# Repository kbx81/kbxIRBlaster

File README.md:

# kbx IR Blaster

## What?

Just another ESP32-based IR Blaster. It was designed with [ESPHome](https://esphome.io) in mind but should work fine
with [Tasmota](https://tasmota.github.io/docs/) or any other app, really.

I've created four versions:
- [v4](v4/)
  - Based on ESP32-C6
  - Nearly identical to [v3](v3/) (below) but with minor adjustments/enhancements
- [v3](v3/)
  - Based on ESP32-C3
  - Disc (smaller)
  - One header for (an) off-board emitter(s)
  - Pads for 24 IR LEDs:
    - Eight top-emitting surface mount
    - Eight side-emitting surface mount around the edges of the disc
    - Eight 5 mm LEDs for extra "throw"
- [v2](v2/)
  - Based on ESP32
  - Disc
  - One header for (an) off-board emitter(s)
  - Pads for 16 IR LEDs:
    - Eight top-emitting surface mount
    - Eight 5 mm LEDs for extra "throw" around the perimeter of the PCB
- [v1](v1/)
  - Based on ESP32
  - Rectangular
  - One header for up to four external control channels
  - Pads for up to eight through-hole LEDs, front- and/or back-facing

See the [gallery](GALLERY.md) for more images.

## Why?

After trying this on a perfboard with parts I had laying around, I wanted something more polished and more powerful.
I found [Sparkfun's IR Blaster](https://www.sparkfun.com/products/15031) which is quite nice, tiny and clean but I
quickly realized that its IR output is somewhat weak and would only work if pointed _directly_ at the device it was
intended to control. Rather than hack it up, I chose to draw up my own versions of such a thing. My goal was to make
them substantially more powerful in an effort to "light up a room" with infrared light; that is, you'll probably find
that they work well even when not specifically directed at (if even near) devices you wish to control. I've used an
ESP32 module instead of an ESP8266, as the ESP32 (and its variants) has dedicated hardware for IR data transmission
(the RMT) which makes it more suitable for this purpose, despite that it's otherwise quite overkill.

## How?

Please see the bill of materials (BoM) for the version of interest:
 -  v4 BoM: [Octopart](https://octopart.com/bom-tool/P6YqtNWD), [CSV](v4/kbxIrBlaster_bom.csv)
 -  v3 BoM: [Octopart](https://octopart.com/bom-tool/GUsHZQub), [CSV](v3/kbxIrBlaster_bom.csv)
 -  v2 BoM: [Octopart](https://octopart.com/bom-tool/78rYOXWE), [CSV](v2/kbxIrBlaster_bom.csv)
 -  v1 BoM: [Octopart](https://octopart.com/bom-tool/vDwq4wDr), [CSV](v1/kbxIrBlaster_bom.csv)

I had the PCBs fabricated by [Elecrow](https://www.elecrow.com) but nearly any PCB fabricator should be able to
manufacture these without any issues. I do recommend white soldermask as it will reflect IR best.

The schematic and PCB were drawn in [KiCad](https://www.kicad.org).

## Build Notes

The [v1](v1/) and [v2](v2/) PCBs have a number of solder jumpers on the bottom side that enable each of the FET drivers
to be connected to one of two possible GPIO pins. This allows a single GPIO pin to control all LEDs simultaneously or
they can be broken apart onto separate GPIO pins. Labels on the underside of the PCBs indicate what jumpers are
connected to what LEDs.

_Note that the solder jumpers **must be bridged** one way or the other; if this is not done, the FETs (and consequently
the LEDs they drive) will not activate!_ When you build one, be sure to complete this step or you'll be left in the
dark. (Punny, I know.)

## Add-ons

An FS1000A (such as [this one](https://www.amazon.com/HiLetgo-Wireless-Transmitter-Receiver-Raspberry/dp/B01DKC2EY4/))
or similar 433 MHz transmitter module may be connected as indicated on the PCB allowing the device to double as an RF
remote controller. On the [v1](v1/) PCB, bridge JP6 to enable this and then connect the module to pins 4, 5, and 6 on
J2. On the [v2](v2/) PCB, simply connect the transmitter to J8. When doing so, be sure to orient the module correctly
or tragedy may result.

## Usage

See my [ESPHome-configs](https://github.com/kbx81/esphome-configs) repository for example
[ESPHome](https://esphome.io) configuration you may use with your IR blaster. Enjoy!

 ## Legal stuff and License

The circuit schematics and PCB found here are licensed under the
 [Creative Commons Attribution-ShareAlike 4.0 International License](http://creativecommons.org/licenses/by-sa/4.0/).

_Happy building!_

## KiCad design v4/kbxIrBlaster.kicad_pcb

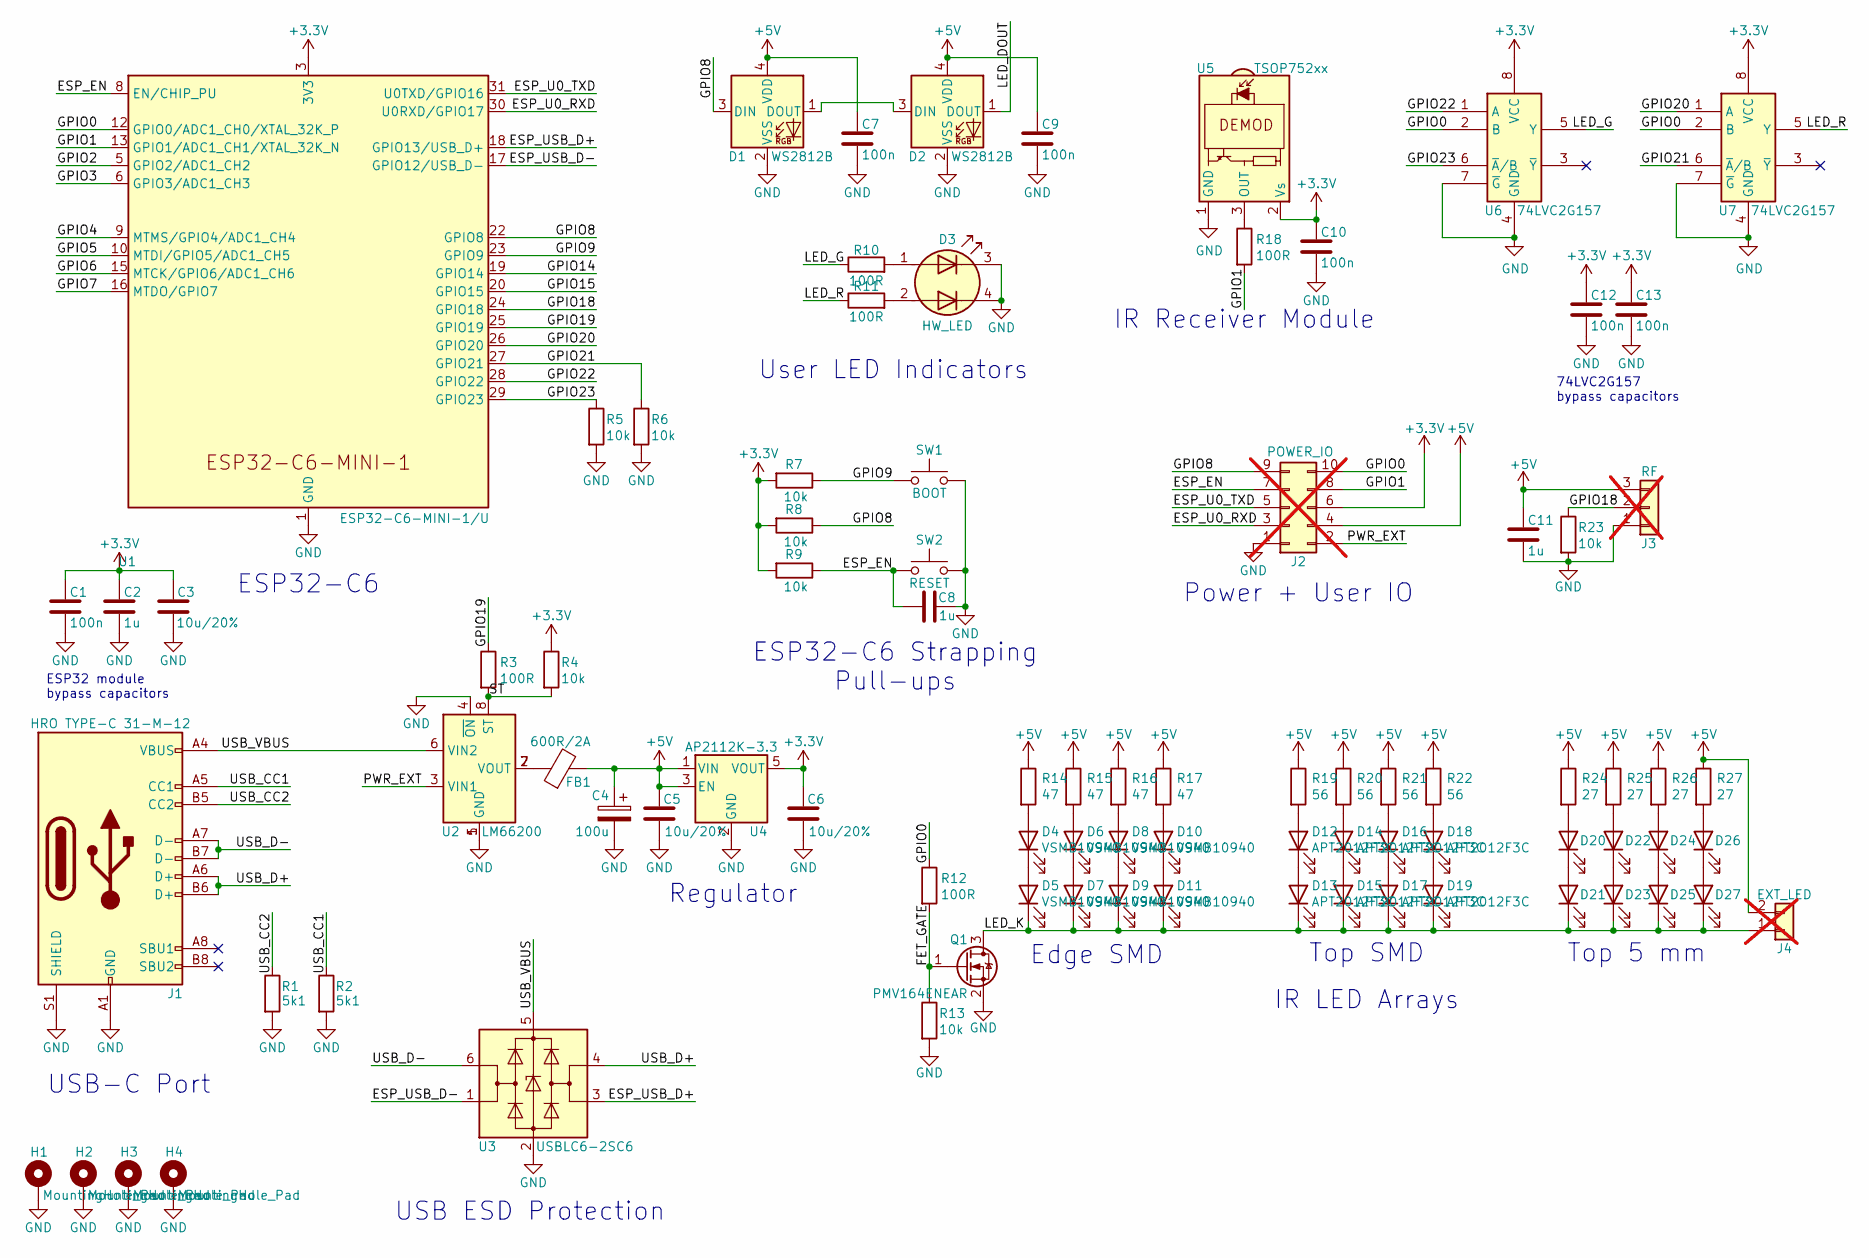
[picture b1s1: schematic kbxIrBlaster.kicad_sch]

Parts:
C1, C7, C9, C10, C12, C13: 100n; C_0402_1005Metric; MPN1 CC0402KRX5R6BB104
C2, C8, C11: 1u; C_0402_1005Metric; MPN1 CC0402KRX5R6BB105
C3, C5, C6: 10u/20%; C_0603_1608Metric; MPN1 CC0603MRX5R6BB106
C4: 100u; CP_Elec_5x5.4; MPN1 UWR1A101MCL1GB
D1, D2: WS2812B; LED_WS2812B-2020_PLCC4_2.0x2.0mm; MPN1 WS2812B-2020
D3: HW_LED; LED_Cree-PLCC4_3.2x2.8mm_CCW; MPN1 APB3227SURKZGC
D4, D5, D6, D7, D8, D9, D10, D11: VSMB10940; LED_Kingbright_KPA-3010_3x2x1mm; MPN1 VSMB10940
D12, D13, D14, D15, D16, D17, D18, D19: APT2012F3C; LED_0805_2012Metric; MPN1 APT2012F3C
D20, D21, D22, D23, D24, D25, D26, D27: LTE-4206; LED_D5.0mm; MPN1 LTE-4206
FB1: 600R/2A; L_0603_1608Metric; MPN1 MPZ1608S221ATA00
H1, H2, H3, H4: MountingHole_Pad; MountingHole_2.5mm_Pad_Via
J1: HRO TYPE-C 31-M-12; USB_C_Receptacle_HRO_TYPE-C-31-M-12; MPN1 HRO TYPE-C 31-M-12
J2: POWER_IO; PinSocket_2x05_P2.54mm_Vertical; not fitted
J3: RF; PinSocket_1x03_P2.54mm_Vertical; not fitted
J4: EXT_LED; PinSocket_1x02_P2.54mm_Vertical; not fitted
Q1: PMV164ENEAR; SOT-23; MPN1 PMV164ENEAR
R1, R2: 5k1; R_0402_1005Metric; MPN1 RC0402JR-075K1L
R3, R10, R11, R12, R18: 100R; R_0402_1005Metric; MPN1 RC0402JR-07100RL
R4, R5, R6, R7, R8, R9, R13, R23: 10k; R_0402_1005Metric; MPN1 RC0402JR-0710KL
R14, R15, R16, R17: 47; R_0805_2012Metric; MPN1 RC0805JR-0747RL
R19, R20, R21, R22: 56; R_0805_2012Metric; MPN1 RC0805JR-0756RL
R24, R25, R26, R27: 27; R_0805_2012Metric; MPN1 RC0805FR-0727RL
SW1: BOOT; SW_Push_1P1T_NO_CK_KMR2; MPN1 KMR2
SW2: RESET; SW_Push_1P1T_NO_CK_KMR2; MPN1 KMR2
U1: ESP32-C6-MINI-1/U; ESP32-C6-MINI-1; MPN1 ESP32-C6-MINI-1
U2: LM66200; SOT-583-8; MPN1 LM66200
U3: USBLC6-2SC6; SOT-23-6; MPN1 USBLC6-2SC6
U4: AP2112K-3.3; SOT-23-5; MPN1 AP2112K-3.3TRG1
U5: TSOP752xx; Vishay_TSOP752_Horizontal; MPN1 TSOP75238
U6, U7: 74LVC2G157; VSSOP-8_2.3x2mm_P0.5mm; MPN1 74LVC2G157

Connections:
+3.3V: C1.1, C2.1, C3.1, C6.1, C10.1, C12.1, C13.1, J2.6, R4.1, R7.2, R8.2, R9.2, U1.3 (3V3), U4.5 (VOUT), U5.2 (Vs), U6.8 (VCC), U7.8 (VCC)
+5V: C4.1, C5.1, C7.1, C9.1, C11.1, D1.4 (VDD), D2.4 (VDD), FB1.2, J2.4, J3.3, J4.2, R14.1, R15.1, R16.1, R17.1, R19.1, R20.1, R21.1, R22.1, R24.1, R25.1, R26.1, R27.1, U4.1 (VIN), U4.3 (EN)
/ESP_EN: C8.1, J2.7, R9.1, SW2.1, U1.8 (EN/CHIP_PU)
/ESP_U0_RXD: J2.3, U1.30 (U0RXD/GPIO17)
/ESP_U0_TXD: J2.5, U1.31 (U0TXD/GPIO16)
/ESP_USB_D+: U1.18 (GPIO13/USB_D+), U3.3 (I/O2)
/ESP_USB_D-: U1.17 (GPIO12/USB_D-), U3.1 (I/O1)
/FET_GATE: Q1.1 (G), R12.2, R13.1
/GPIO0: J2.10, R12.1, U1.12 (GPIO0/ADC1_CH0/XTAL_32K_P), U6.2 (B), U7.2 (B)
/GPIO1: J2.8, R18.2, U1.13 (GPIO1/ADC1_CH1/XTAL_32K_N)
/GPIO2: U1.5 (GPIO2/ADC1_CH2)
/GPIO3: U1.6 (GPIO3/ADC1_CH3)
/GPIO4: U1.9 (MTMS/GPIO4/ADC1_CH4)
/GPIO5: U1.10 (MTDI/GPIO5/ADC1_CH5)
/GPIO6: U1.15 (MTCK/GPIO6/ADC1_CH6)
/GPIO7: U1.16 (MTDO/GPIO7)
/GPIO8: D1.3 (DIN), J2.9, R8.1, U1.22 (GPIO8)
/GPIO9: R7.1, SW1.1, U1.23 (GPIO9)
/GPIO14: U1.19 (GPIO14)
/GPIO15: U1.20 (GPIO15)
/GPIO18: J3.2, R23.1, U1.24 (GPIO18)
/GPIO19: R3.1, U1.25 (GPIO19)
/GPIO20: U1.26 (GPIO20), U7.1 (A)
/GPIO21: R6.1, U1.27 (GPIO21), U7.6 (~A/B)
/GPIO22: U1.28 (GPIO22), U6.1 (A)
/GPIO23: R5.1, U1.29 (GPIO23), U6.6 (~A/B)
/LED_DOUT: D2.1 (DOUT)
/LED_G: R10.1, U6.5 (Y)
/LED_K: D5.1 (K), D7.1 (K), D9.1 (K), D11.1 (K), D13.1 (K), D15.1 (K), D17.1 (K), D19.1 (K), D21.1 (K), D23.1 (K), D25.1 (K), D27.1 (K), J4.1, Q1.3 (D)
/LED_R: R11.1, U7.5 (Y)
/PWR_EXT: J2.2, U2.3 (VIN1)
/ST: R3.2, R4.2, U2.8 (ST)
/USB_CC1: J1.A5 (CC1), R2.1
/USB_CC2: J1.B5 (CC2), R1.1
/USB_D+: J1.A6 (D+), J1.B6 (D+), U3.4 (I/O2)
/USB_D-: J1.A7 (D-), J1.B7 (D-), U3.6 (I/O1)
/USB_VBUS: J1.A4 (VBUS), J1.A9 (VBUS), J1.B4 (VBUS), J1.B9 (VBUS), U2.6 (VIN2), U3.5 (VBUS)
GND: C1.2, C2.2, C3.2, C4.2, C5.2, C6.2, C7.2, C8.2, C9.2, C10.2, C11.2, C12.2, C13.2, D1.2 (VSS), D2.2 (VSS), D3.3 (K1), D3.4 (K2), H1.1, H2.1, H3.1, H4.1, J1.A1 (GND), J1.A12 (GND), J1.B1 (GND), J1.B12 (GND), J1.S1 (SHIELD), J2.1, J3.1, Q1.2 (S), R1.2, R2.2, R5.2, R6.2, R13.2, R23.2, SW1.2, SW2.2, U1.1 (GND), U1.2 (GND), U1.11 (GND), U1.14 (GND), U1.36 (GND), U1.37 (GND), U1.38 (GND), U1.39 (GND), U1.40 (GND), U1.41 (GND), U1.42 (GND), U1.43 (GND), U1.44 (GND), U1.45 (GND), U1.46 (GND), U1.47 (GND), U1.48 (GND), U1.49 (GND), U1.50 (GND), U1.51 (GND), U1.52 (GND), U1.53 (GND), U2.1 (GND), U2.4 (~ON), U2.5 (GND), U3.2 (GND), U4.2 (GND), U5.1 (GND), U5.4 (GND), U6.4 (GND), U6.7 (~G), U7.4 (GND), U7.7 (~G)
unnamed: D1.1 (DOUT), D2.3 (DIN)
unnamed: D3.1 (A1), R10.2
unnamed: D3.2 (A2), R11.2
unnamed: D4.2 (A), R14.2
unnamed: D4.1 (K), D5.2 (A)
unnamed: D6.2 (A), R15.2
unnamed: D6.1 (K), D7.2 (A)
unnamed: D8.2 (A), R16.2
unnamed: D8.1 (K), D9.2 (A)
unnamed: D10.2 (A), R17.2
unnamed: D10.1 (K), D11.2 (A)
unnamed: D12.2 (A), R19.2
unnamed: D12.1 (K), D13.2 (A)
unnamed: D14.2 (A), R20.2
unnamed: D14.1 (K), D15.2 (A)
unnamed: D16.2 (A), R21.2
unnamed: D16.1 (K), D17.2 (A)
unnamed: D18.2 (A), R22.2
unnamed: D18.1 (K), D19.2 (A)
unnamed: D20.2 (A), R24.2
unnamed: D20.1 (K), D21.2 (A)
unnamed: D22.2 (A), R25.2
unnamed: D22.1 (K), D23.2 (A)
unnamed: D24.2 (A), R26.2
unnamed: D24.1 (K), D25.2 (A)
unnamed: D26.2 (A), R27.2
unnamed: D26.1 (K), D27.2 (A)
unnamed: FB1.1, U2.2 (VOUT), U2.7 (VOUT)
unnamed: R18.1, U5.3 (OUT)

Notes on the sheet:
Top SMD
Edge SMD
74LVC2G157 bypass capacitors
User LED Indicators
Power + User IO
ESP32-C6
USB-C Port
USB ESD Protection
Top 5 mm
ESP32-C6 Strapping Pull-ups
IR Receiver Module
IR LED Arrays
Regulator
ESP32 module bypass capacitors

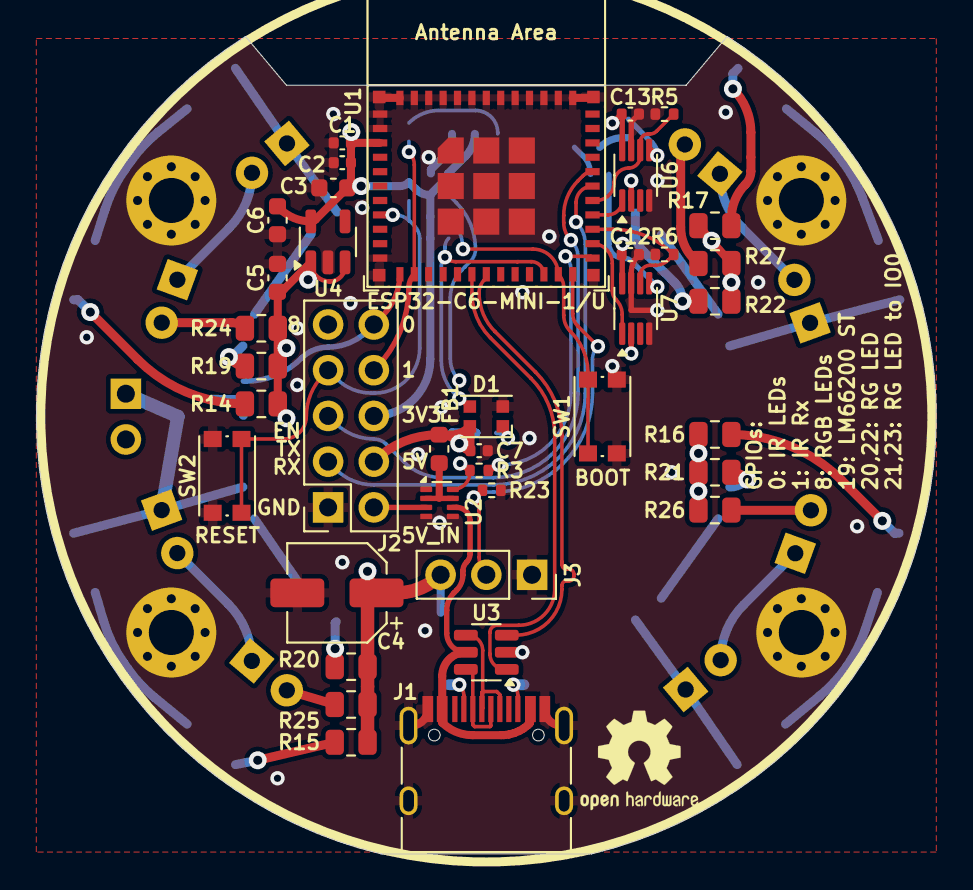
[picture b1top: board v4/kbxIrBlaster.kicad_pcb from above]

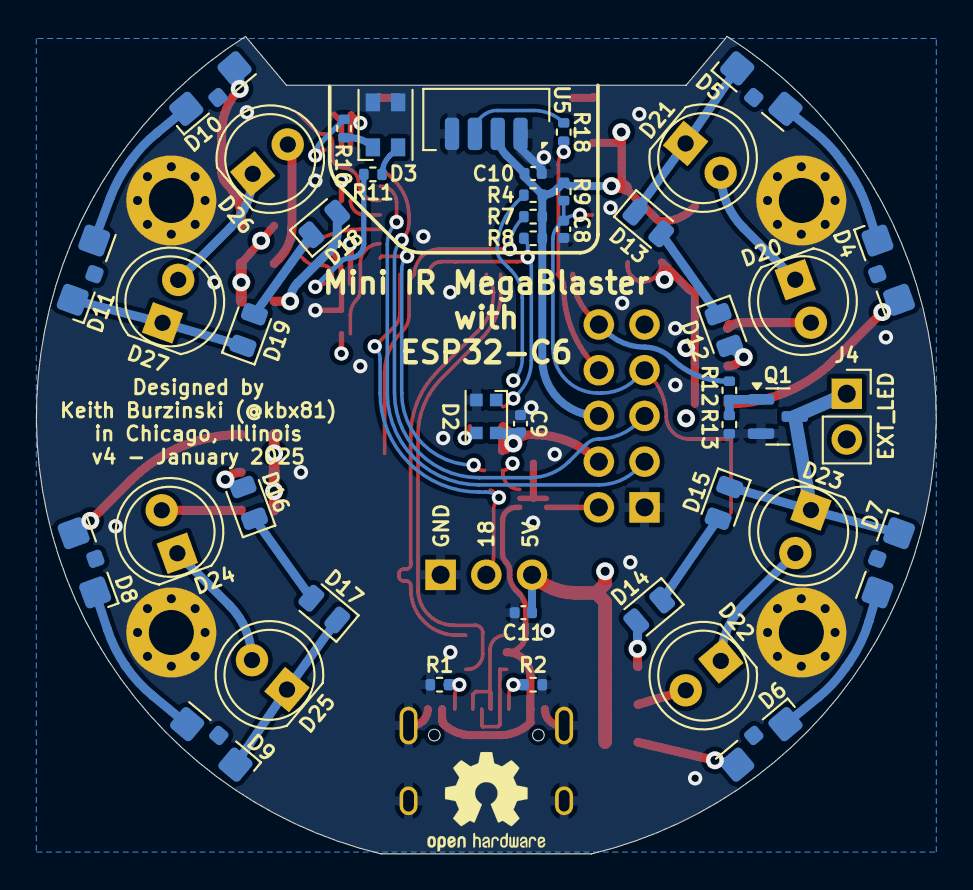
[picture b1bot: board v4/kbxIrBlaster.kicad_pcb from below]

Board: 4 copper layers, 50.0 x 45.4 mm, 86 parts (44 on the bottom side), 58 nets.

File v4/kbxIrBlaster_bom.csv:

Component,Quantity Per PCB,References,Value,MPN1,MPN2,Footprint,Population
1,6,C1 C7 C9 C10 C12 C13,100n,CC0402KRX5R6BB104,,C_0402_1005Metric,
2,3,C2 C8 C11,1u,CC0402KRX5R6BB105,,C_0402_1005Metric,
3,1,C4,100u,UWR1A101MCL1GB,,CP_Elec_5x5.4,
4,3,C3 C5 C6,10u/20%,CC0603MRX5R6BB106,,C_0603_1608Metric,
5,8,D12 D13 D14 D15 D16 D17 D18 D19,APT2012F3C,APT2012F3C,,LED_0805_2012Metric,
6,1,D3,HW_LED,APB3227SURKZGC,,LED_Cree-PLCC4_3.2x2.8mm_CCW,
7,8,D20 D21 D22 D23 D24 D25 D26 D27,LTE-4206,LTE-4206,,LED_D5.0mm,
8,8,D4 D5 D6 D7 D8 D9 D10 D11,VSMB10940,VSMB10940,,LED_Kingbright_KPA-3010_3x2x1mm,
9,2,D1 D2,WS2812B,WS2812B-2020,,LED_WS2812B-2020_PLCC4_2.0x2.0mm,
10,1,FB1,600R/2A,MPZ1608S221ATA00,,L_0603_1608Metric,
11,1,J1,HRO TYPE-C 31-M-12,HRO TYPE-C 31-M-12,,USB_C_Receptacle_HRO_TYPE-C-31-M-12,
12,1,Q1,PMV164ENEAR,PMV164ENEAR,,SOT-23,
13,4,R24 R25 R26 R27,27,RC0805FR-0727RL,,R_0805_2012Metric,
14,4,R14 R15 R16 R17,47,RC0805JR-0747RL,,R_0805_2012Metric,
15,4,R19 R20 R21 R22,56,RC0805JR-0756RL,,R_0805_2012Metric,
16,5,R3 R10 R11 R12 R18,100R,RC0402JR-07100RL,,R_0402_1005Metric,
17,2,R1 R2,5k1,RC0402JR-075K1L,,R_0402_1005Metric,
18,8,R4 R5 R6 R7 R8 R9 R13 R23,10k,RC0402JR-0710KL,,R_0402_1005Metric,
19,2,SW1 SW2,BOOT,KMR2,,SW_Push_1P1T_NO_CK_KMR2,
20,2,U6 U7,74LVC2G157,74LVC2G157,,VSSOP-8_2.3x2mm_P0.5mm,
21,1,U4,AP2112K-3.3,AP2112K-3.3TRG1,,SOT-23-5,
22,1,U1,ESP32-C6-MINI-1/U,ESP32-C6-MINI-1,,ESP32-C6-MINI-1,
23,1,U2,LM66200,LM66200,,SOT-583-8,
24,1,U5,TSOP752xx,TSOP75238,,Vishay_TSOP752_Horizontal,
25,1,U3,USBLC6-2SC6,USBLC6-2SC6,,SOT-23-6,

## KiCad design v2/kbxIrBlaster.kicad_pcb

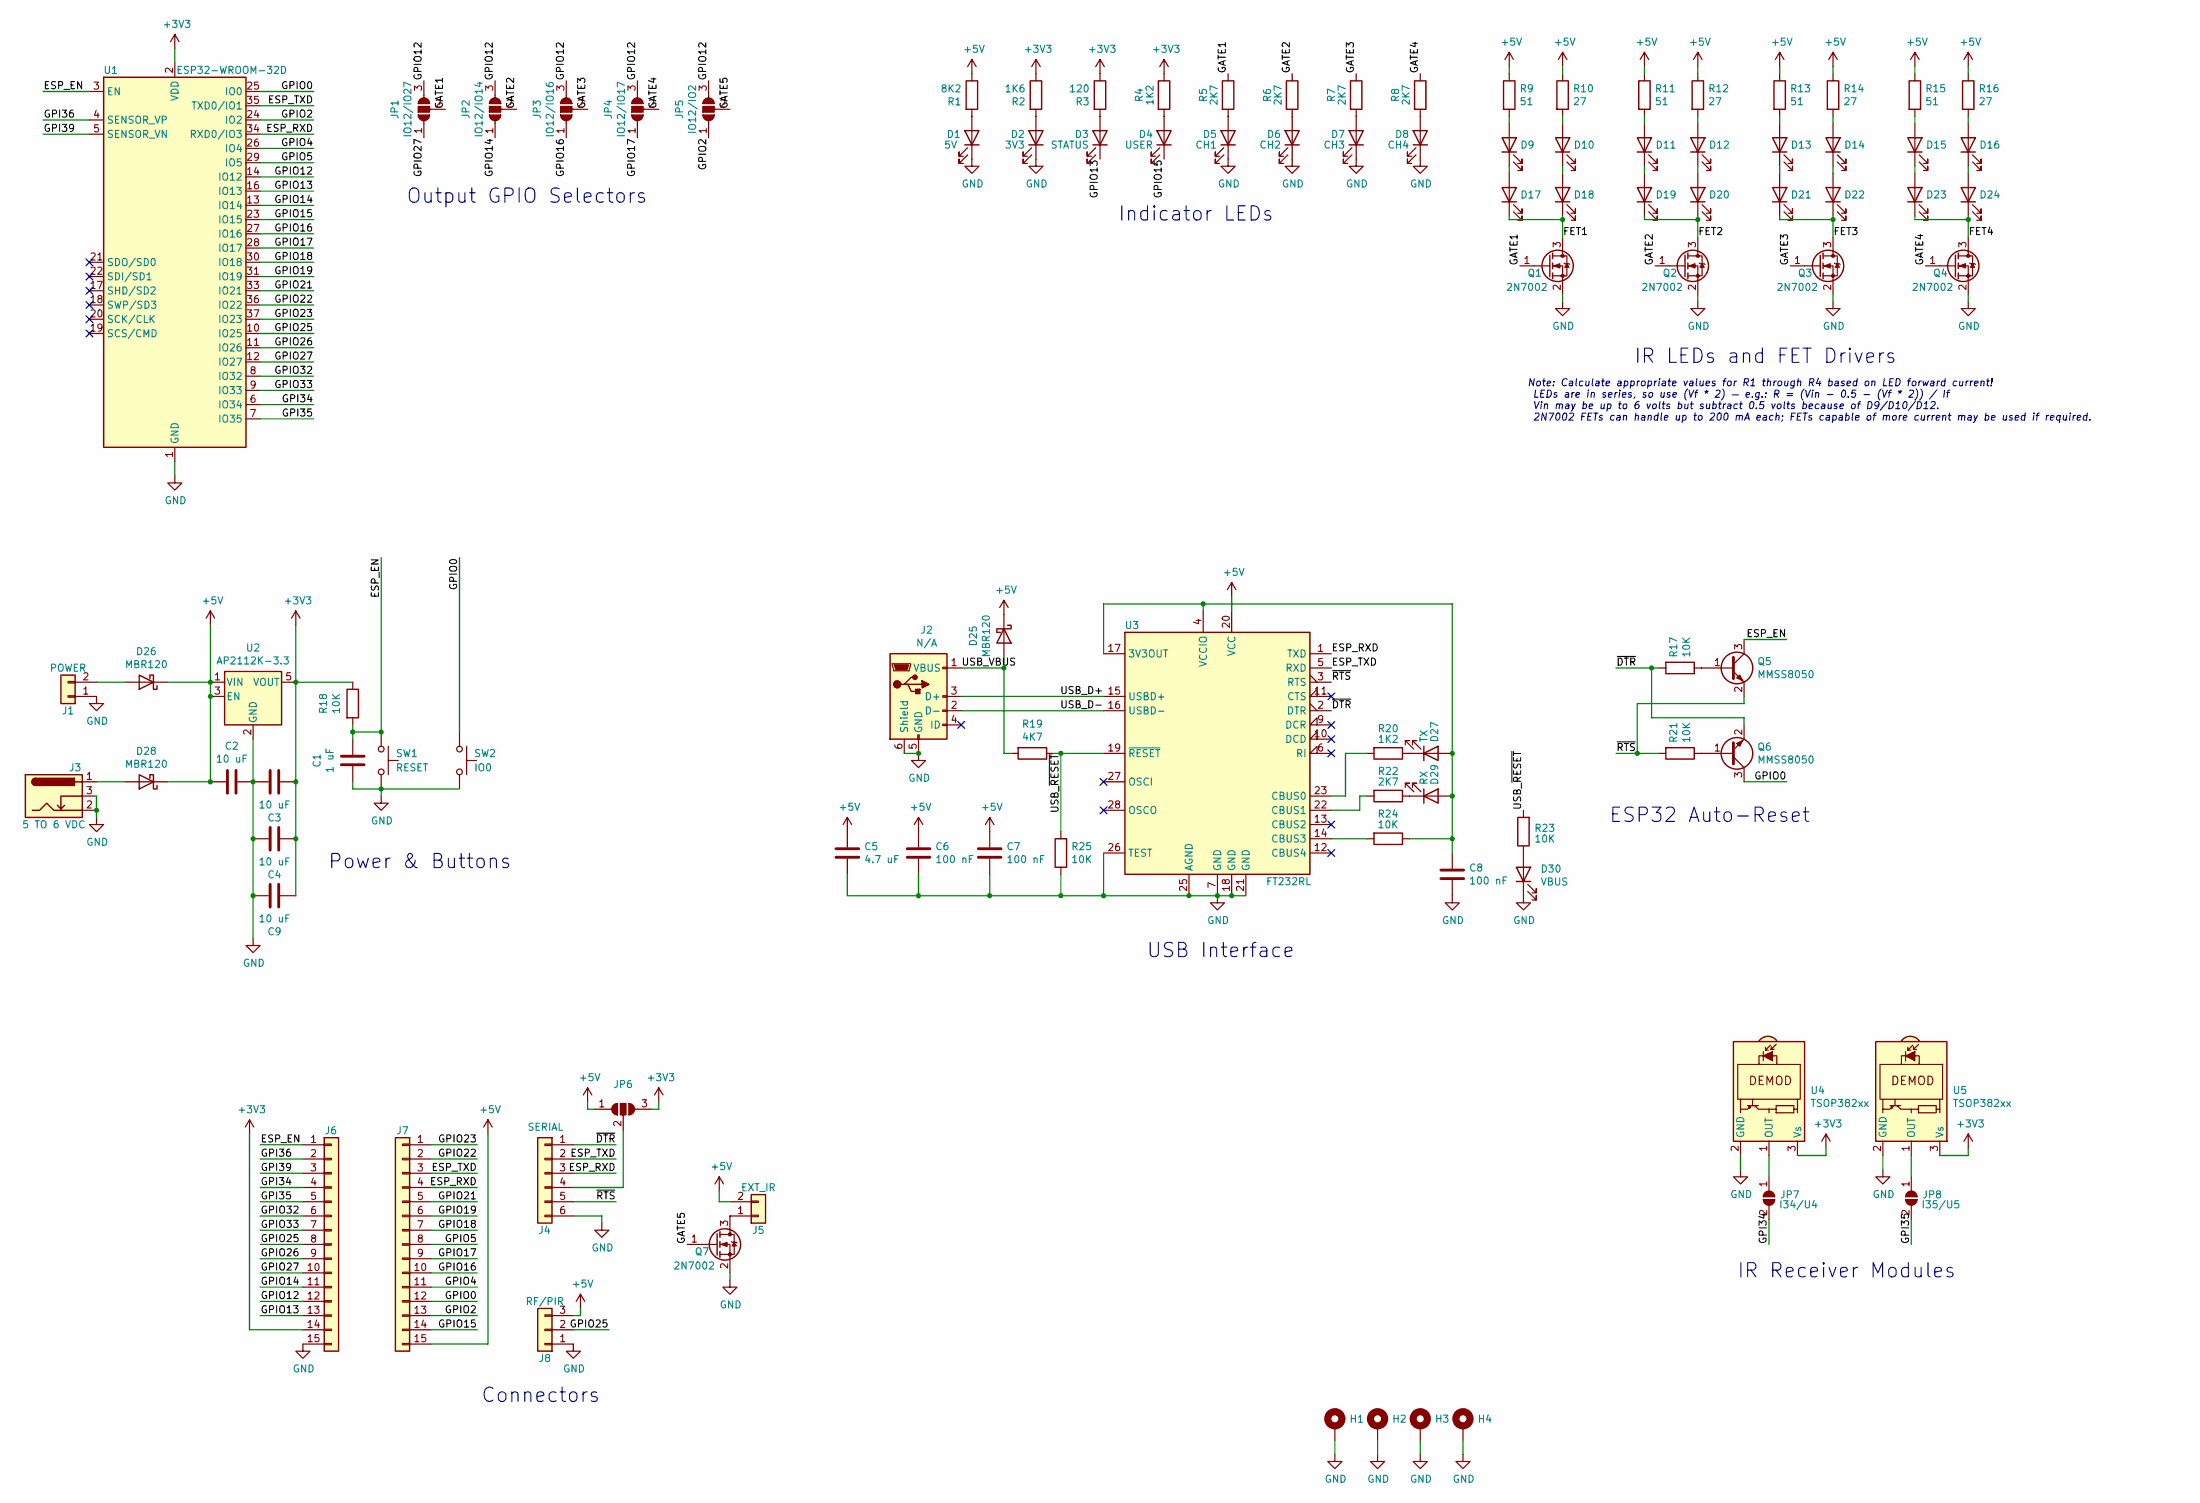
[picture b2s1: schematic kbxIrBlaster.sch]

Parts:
C1: 1 uF; C_0805_2012Metric; MPN1 C0805C105K4RACTU
C2, C3, C4, C9: 10 uF; C_0805_2012Metric; MPN1 GRM21BC81C106ME15L
C5: 4.7 uF; C_0805_2012Metric; MPN1 C2012X5R1H475K125AB
C6, C7, C8: 100 nF; C_0805_2012Metric; MPN1 CC0805KRX7R7BB104
D1: 5V; LED_0805_2012Metric; MPN1 LSM0805543V
D2: 3V3; LED_0805_2012Metric; MPN1 LSM0805543V
D3: STATUS; LED_0805_2012Metric; MPN1 APT2012SECK
D4: USER; LED_0805_2012Metric; MPN1 APT2012SYCK
D5: CH1; LED_0805_2012Metric; MPN1 APT2012EC
D6: CH2; LED_0805_2012Metric; MPN1 APT2012EC
D7: CH3; LED_0805_2012Metric; MPN1 APT2012EC
D8: CH4; LED_0805_2012Metric; MPN1 APT2012EC
D9, D17: CH1; LED_0805_2012Metric; MPN1 APT2012F3C
D10, D18: CH1; LED_D5.0mm; MPN1 LTE-4206
D11, D19: CH2; LED_0805_2012Metric; MPN1 APT2012F3C
D12, D20: CH2; LED_D5.0mm; MPN1 LTE-4206
D13, D21: CH3; LED_0805_2012Metric; MPN1 APT2012F3C
D14, D22: CH3; LED_D5.0mm; MPN1 LTE-4206
D15, D23: CH4; LED_0805_2012Metric; MPN1 APT2012F3C
D16, D24: CH4; LED_D5.0mm; MPN1 LTE-4206
D25, D26, D28: MBR120; D_SOD-123F; MPN1 MBR120VLSFT1G
D27: TX; LED_0805_2012Metric; MPN1 APT2012VBC/D
D29: RX; LED_0805_2012Metric; MPN1 APT2012EC
D30: VBUS; LED_0805_2012Metric; MPN1 APT2012ZGCK
H1, H2, H3, H4: -; MountingHole_2.5mm_Pad_Via
J1: POWER; PinHeader_1x02_P2.54mm_Vertical
J2: N/A; USB_Micro-B_Molex-105017-0001; MPN1 105017-0001
J3: 5 TO 6 VDC; BarrelJack_Horizontal; MPN1 163-179PH-EX
J4: SERIAL; PinHeader_1x06_P2.54mm_Vertical
J5: EXT_IR; PinHeader_1x02_P2.54mm_Vertical
J6, J7: IO; PinHeader_1x15_P2.54mm_Vertical
J8: RF/PIR; PinHeader_1x03_P2.54mm_Vertical
JP1: IO12/IO27; SolderJumper-3_P1.3mm_Open_RoundedPad1.0x1.5mm
JP2: IO12/IO14; SolderJumper-3_P1.3mm_Open_RoundedPad1.0x1.5mm
JP3: IO12/IO16; SolderJumper-3_P1.3mm_Open_RoundedPad1.0x1.5mm
JP4: IO12/IO17; SolderJumper-3_P1.3mm_Open_RoundedPad1.0x1.5mm
JP5: IO12/IO2; SolderJumper-3_P1.3mm_Open_RoundedPad1.0x1.5mm
JP6: 5V/3V3; SolderJumper-3_P1.3mm_Open_RoundedPad1.0x1.5mm
JP7: I34/U4; SolderJumper-2_P1.3mm_Open_RoundedPad1.0x1.5mm
JP8: I35/U5; SolderJumper-2_P1.3mm_Open_RoundedPad1.0x1.5mm
Q1, Q2, Q3, Q4, Q7: 2N7002; SOT-23; MPN1 2N7002-7-F
Q5, Q6: MMSS8050; SOT-23; MPN1 MMSS8050
R1: 8K2; R_0805_2012Metric; MPN1 RT0805FRE078K2L
R2: 1K6; R_0805_2012Metric; MPN1 RT0805FRE071K6L
R3: 120; R_0805_2012Metric; MPN1 RT0805FRE07120RL
R4, R20: 1K2; R_0805_2012Metric; MPN1 RT0805FRE072K7L
R5, R6, R7, R8, R22: 2K7; R_0805_2012Metric; MPN1 RT0805FRE072K7L
R9, R11, R13, R15: 51; R_0805_2012Metric; MPN1 RC0805FR-0751RL
R10, R12, R14, R16: 27; R_0805_2012Metric; MPN1 RC0805FR-0727RL
R17, R18, R21, R23, R24, R25: 10K; R_0805_2012Metric; MPN1 RC0805FR-0710KL
R19: 4K7; R_0805_2012Metric; MPN1 RT0805FRE074K7L
SW1: RESET; SW_Tactile_SPST_Angled_PTS645Vx58-2LFS; MPN1 PTS645VK582LFS
SW2: IO0; SW_Tactile_SPST_Angled_PTS645Vx58-2LFS; MPN1 PTS645VK582LFS
U1: ESP32-WROOM-32D; ESP32-WROOM-32; MPN1 ESP32-WROOM-32D
U2: AP2112K-3.3; SOT-23-5; MPN1 AP2112M-3.3TRG1
U3: FT232RL; SSOP-28_5.3x10.2mm_P0.65mm; MPN1 FT232RL
U4: TSOP382xx; Vishay_MINICAST-3Pin; MPN1 TSOP38238
U5: TSOP382xx; Vishay_MINICAST-3Pin; MPN1 TSOP38256

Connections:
+3V3: C3.2, C4.2, C9.2, J6.14, JP6.3 (B), R2.1, R3.1, R4.1, R18.1, U1.2 (VDD), U2.5 (VOUT), U4.3 (Vs), U5.3 (Vs)
+5V: C2.2, C5.1, C6.1, C7.1, D25.1 (K), D26.1 (K), D28.1 (K), J5.2, J7.15, J8.3, JP6.1 (A), R1.1, R9.1, R10.1, R11.1, R12.1, R13.1, R14.1, R15.1, R16.1, U2.1 (VIN), U2.3 (EN), U3.20 (VCC)
/ESP_EN: C1.1, J6.1, Q5.3 (C), R18.2, SW1.1, U1.3 (EN)
/ESP_RXD: J4.3, J7.4, U1.34 (RXD0/IO3), U3.1 (TXD)
/ESP_TXD: J4.2, J7.3, U1.35 (TXD0/IO1), U3.5 (RXD)
/FET1: D17.1 (K), D18.1 (K), Q1.3 (D)
/FET2: D19.1 (K), D20.1 (K), Q2.3 (D)
/FET3: D21.1 (K), D22.1 (K), Q3.3 (D)
/FET4: D23.1 (K), D24.1 (K), Q4.3 (D)
/GATE1: JP1.2 (C), Q1.1 (G), R5.1
/GATE2: JP2.2 (C), Q2.1 (G), R6.1
/GATE3: JP3.2 (C), Q3.1 (G), R7.1
/GATE4: JP4.2 (C), Q4.1 (G), R8.1
/GATE5: JP5.2 (C), Q7.1 (G)
/GPI34: J6.4, JP7.2 (B), U1.6 (IO34)
/GPI35: J6.5, JP8.2 (B), U1.7 (IO35)
/GPI36: J6.2, U1.4 (SENSOR_VP)
/GPI39: J6.3, U1.5 (SENSOR_VN)
/GPIO0: J7.12, Q6.3 (C), SW2.1, U1.25 (IO0)
/GPIO2: J7.13, JP5.1 (A), U1.24 (IO2)
/GPIO4: J7.11, U1.26 (IO4)
/GPIO5: J7.8, U1.29 (IO5)
/GPIO12: J6.12, JP1.3 (B), JP2.3 (B), JP3.3 (B), JP4.3 (B), JP5.3 (B), U1.14 (IO12)
/GPIO13: D3.1 (K), J6.13, U1.16 (IO13)
/GPIO14: J6.11, JP2.1 (A), U1.13 (IO14)
/GPIO15: D4.1 (K), J7.14, U1.23 (IO15)
/GPIO16: J7.10, JP3.1 (A), U1.27 (IO16)
/GPIO17: J7.9, JP4.1 (A), U1.28 (IO17)
/GPIO18: J7.7, U1.30 (IO18)
/GPIO19: J7.6, U1.31 (IO19)
/GPIO21: J7.5, U1.33 (IO21)
/GPIO22: J7.2, U1.36 (IO22)
/GPIO23: J7.1, U1.37 (IO23)
/GPIO25: J6.8, J8.2, U1.10 (IO25)
/GPIO26: J6.9, U1.11 (IO26)
/GPIO27: J6.10, JP1.1 (A), U1.12 (IO27)
/GPIO32: J6.6, U1.8 (IO32)
/GPIO33: J6.7, U1.9 (IO33)
/USB_D+: J2.3 (D+), U3.15 (USBD+)
/USB_D-: J2.2 (D-), U3.16 (USBD-)
/USB_VBUS: D25.2 (A), J2.1 (VBUS), R19.2
/USB_~RESET: R19.1, R23.2, R25.2, U3.19 (~RESET~)
/~DTR: J4.1, Q6.2 (E), R17.2, U3.2 (DTR)
/~RTS: J4.5, Q5.2 (E), R21.2, U3.3 (RTS)
GND: C1.2, C2.1, C3.1, C4.1, C5.2, C6.2, C7.2, C8.2, C9.1, D1.1 (K), D2.1 (K), D5.1 (K), D6.1 (K), D7.1 (K), D8.1 (K), D30.1 (K), H1.1, H2.1, H3.1, H4.1, J1.1, J2.5 (GND), J2.6 (Shield), J3.2, J3.3, J4.6, J6.15, J8.1, Q1.2 (S), Q2.2 (S), Q3.2 (S), Q4.2 (S), Q7.2 (S), R25.1, SW1.2, SW2.2, U1.1 (GND), U1.15 (GND), U1.38 (GND), U1.39 (GND), U2.2 (GND), U3.7 (GND), U3.18 (GND), U3.21 (GND), U3.25 (AGND), U3.26 (TEST), U4.2 (GND), U5.2 (GND)
unnamed: C8.1, D27.2 (A), D29.2 (A), R24.1, U3.4 (VCCIO), U3.17 (3V3OUT)
unnamed: D1.2 (A), R1.2
unnamed: D2.2 (A), R2.2
unnamed: D3.2 (A), R3.2
unnamed: D4.2 (A), R4.2
unnamed: D5.2 (A), R5.2
unnamed: D6.2 (A), R6.2
unnamed: D7.2 (A), R7.2
unnamed: D8.2 (A), R8.2
unnamed: D9.2 (A), R9.2
unnamed: D10.1 (K), D18.2 (A)
unnamed: D10.2 (A), R10.2
unnamed: D11.1 (K), D19.2 (A)
unnamed: D11.2 (A), R11.2
unnamed: D12.1 (K), D20.2 (A)
unnamed: D12.2 (A), R12.2
unnamed: D13.1 (K), D21.2 (A)
unnamed: D13.2 (A), R13.2
unnamed: D14.1 (K), D22.2 (A)
unnamed: D14.2 (A), R14.2
unnamed: D15.1 (K), D23.2 (A)
unnamed: D15.2 (A), R15.2
unnamed: D16.1 (K), D24.2 (A)
unnamed: D16.2 (A), R16.2
unnamed: D9.1 (K), D17.2 (A)
unnamed: D26.2 (A), J1.2
unnamed: D27.1 (K), R20.1
unnamed: D28.2 (A), J3.1
unnamed: D29.1 (K), R22.1
unnamed: D30.2 (A), R23.1
unnamed: J4.4, JP6.2 (C)
unnamed: J5.1, Q7.3 (D)
unnamed: JP7.1 (A), U4.1 (OUT)
unnamed: JP8.1 (A), U5.1 (OUT)
unnamed: Q5.1 (B), R17.1
unnamed: Q6.1 (B), R21.1
unnamed: R20.2, U3.23 (CBUS0)
unnamed: R22.2, U3.22 (CBUS1)
unnamed: R24.2, U3.14 (CBUS3)

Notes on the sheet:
IR Receiver Modules
Power & Buttons
ESP32 Auto-Reset
USB Interface
IR LEDs and FET Drivers
Connectors
Note: Calculate appropriate values for R1 through R4 based on LED forward current! LEDs are in series, so use (Vf * 2) — e.g.: R = (Vin - 0.5 - (Vf * 2)) / If Vin may be up to 6 volts but subtract 0.5 volts because of D9/D10/D12. 2N7002 FETs can handle up to 200 mA each; FETs capable of more curren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
Indicator LEDs
Output GPIO Selectors

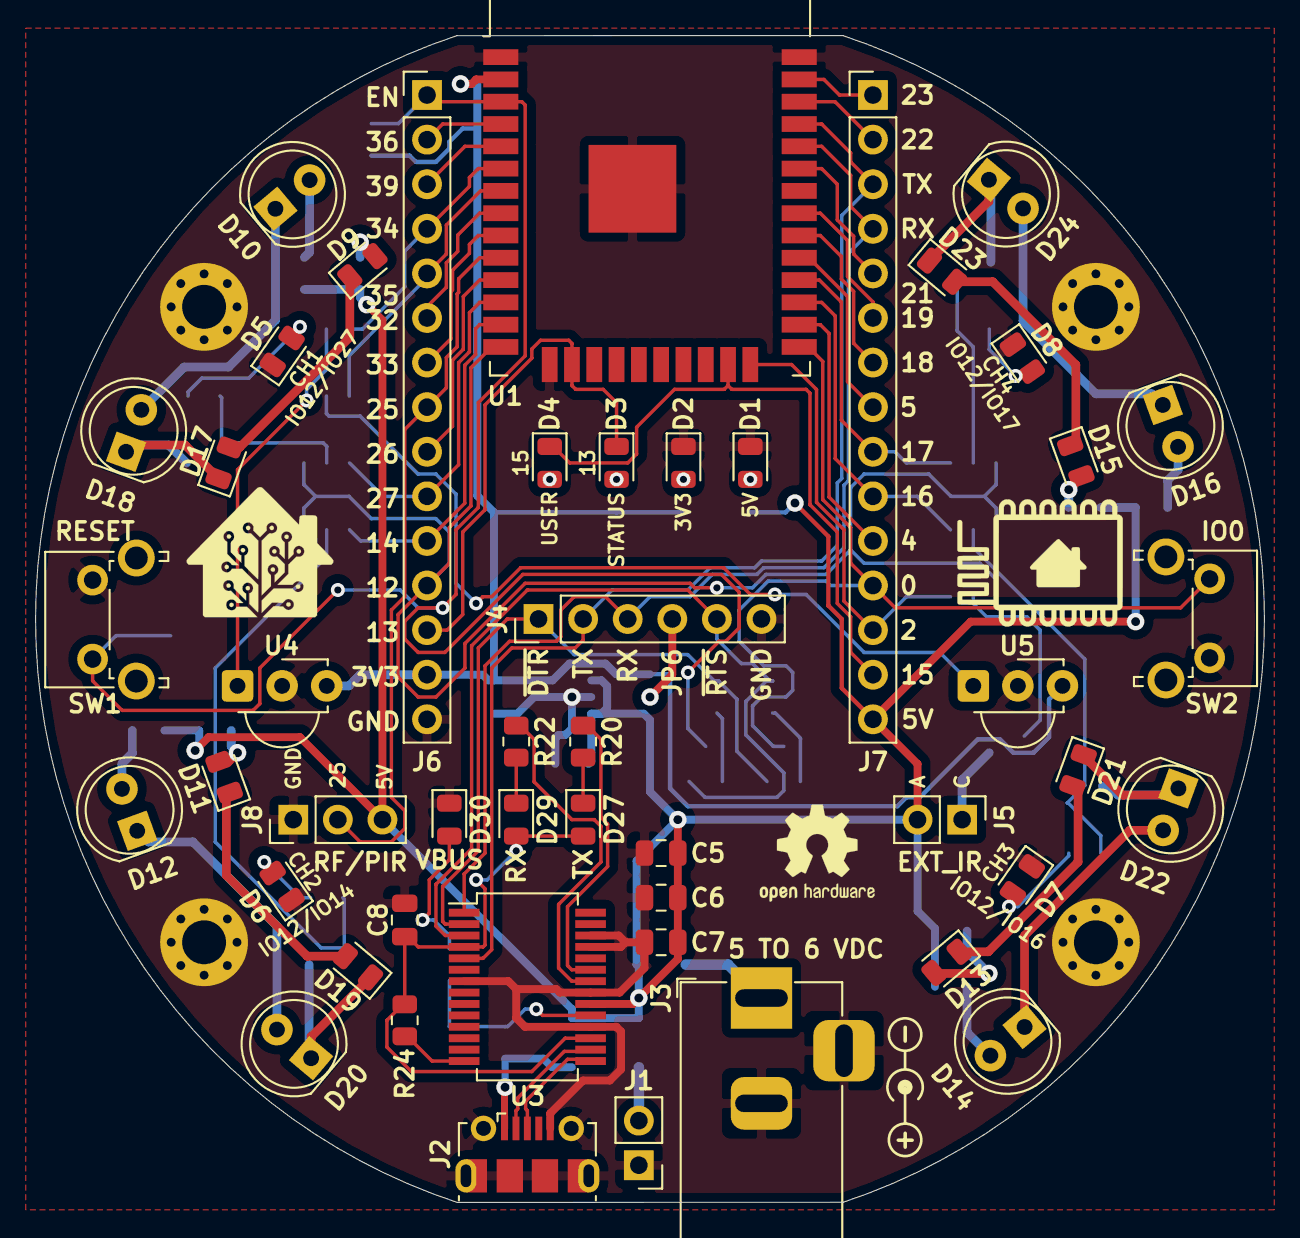
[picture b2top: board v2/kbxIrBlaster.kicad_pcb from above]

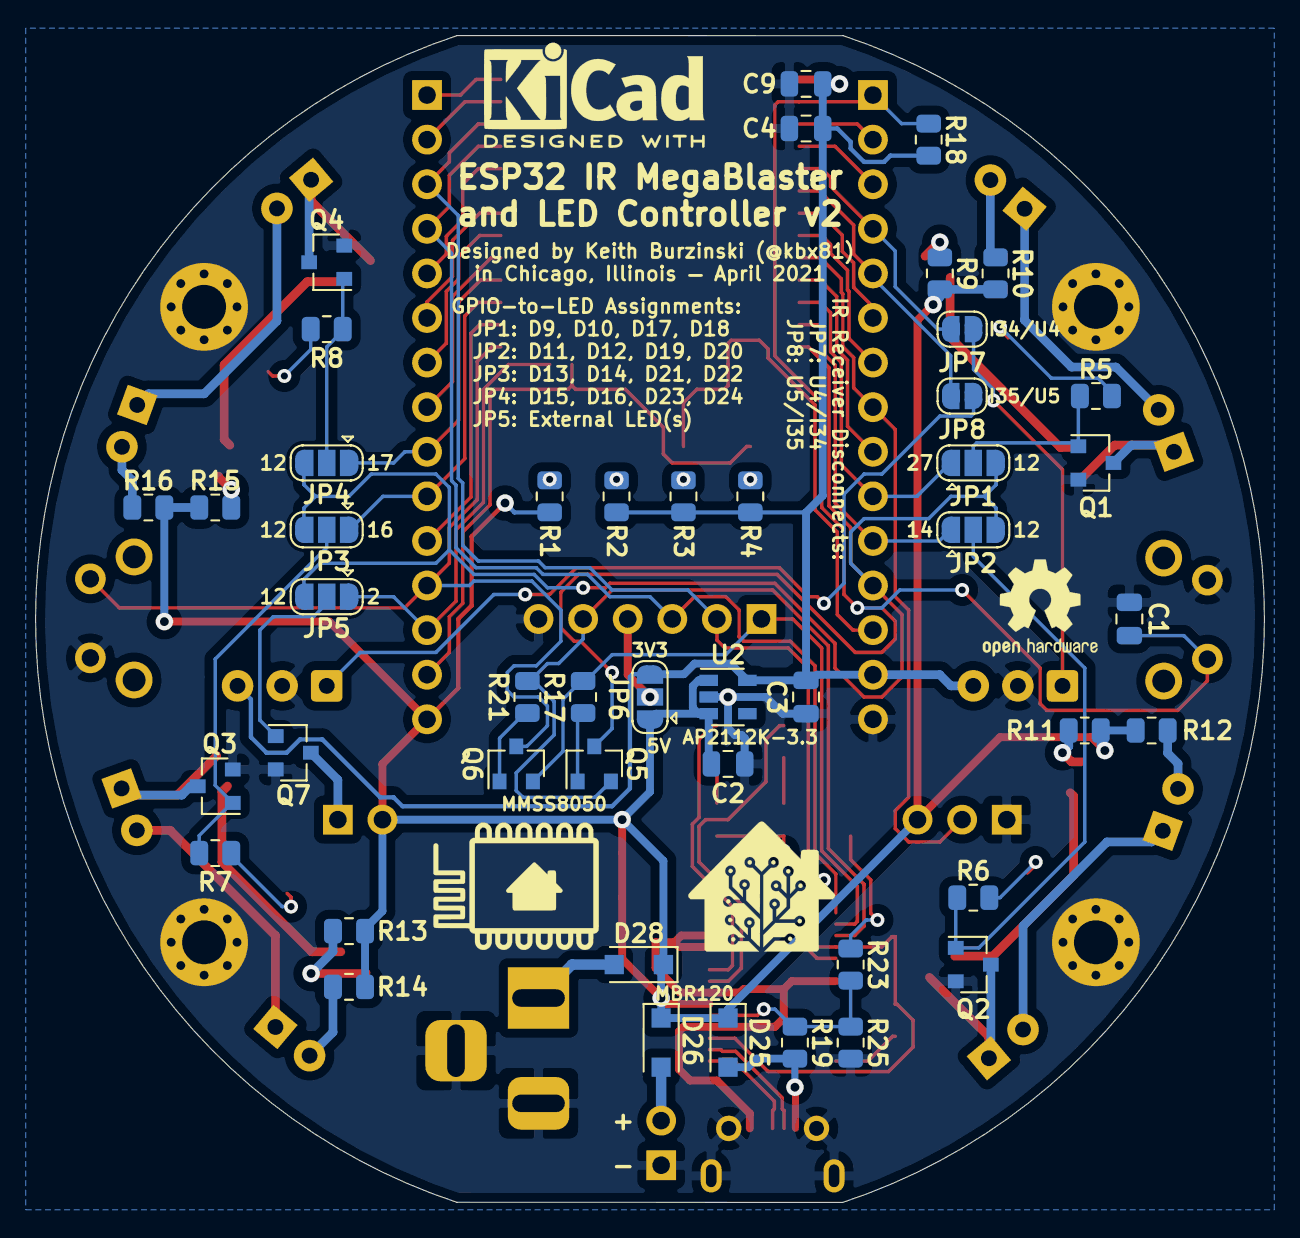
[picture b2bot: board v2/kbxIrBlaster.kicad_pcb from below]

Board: 2 copper layers, 70.0 x 66.5 mm, 98 parts (46 on the bottom side), 84 nets.

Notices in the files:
README.md:
Creative Commons License badge
